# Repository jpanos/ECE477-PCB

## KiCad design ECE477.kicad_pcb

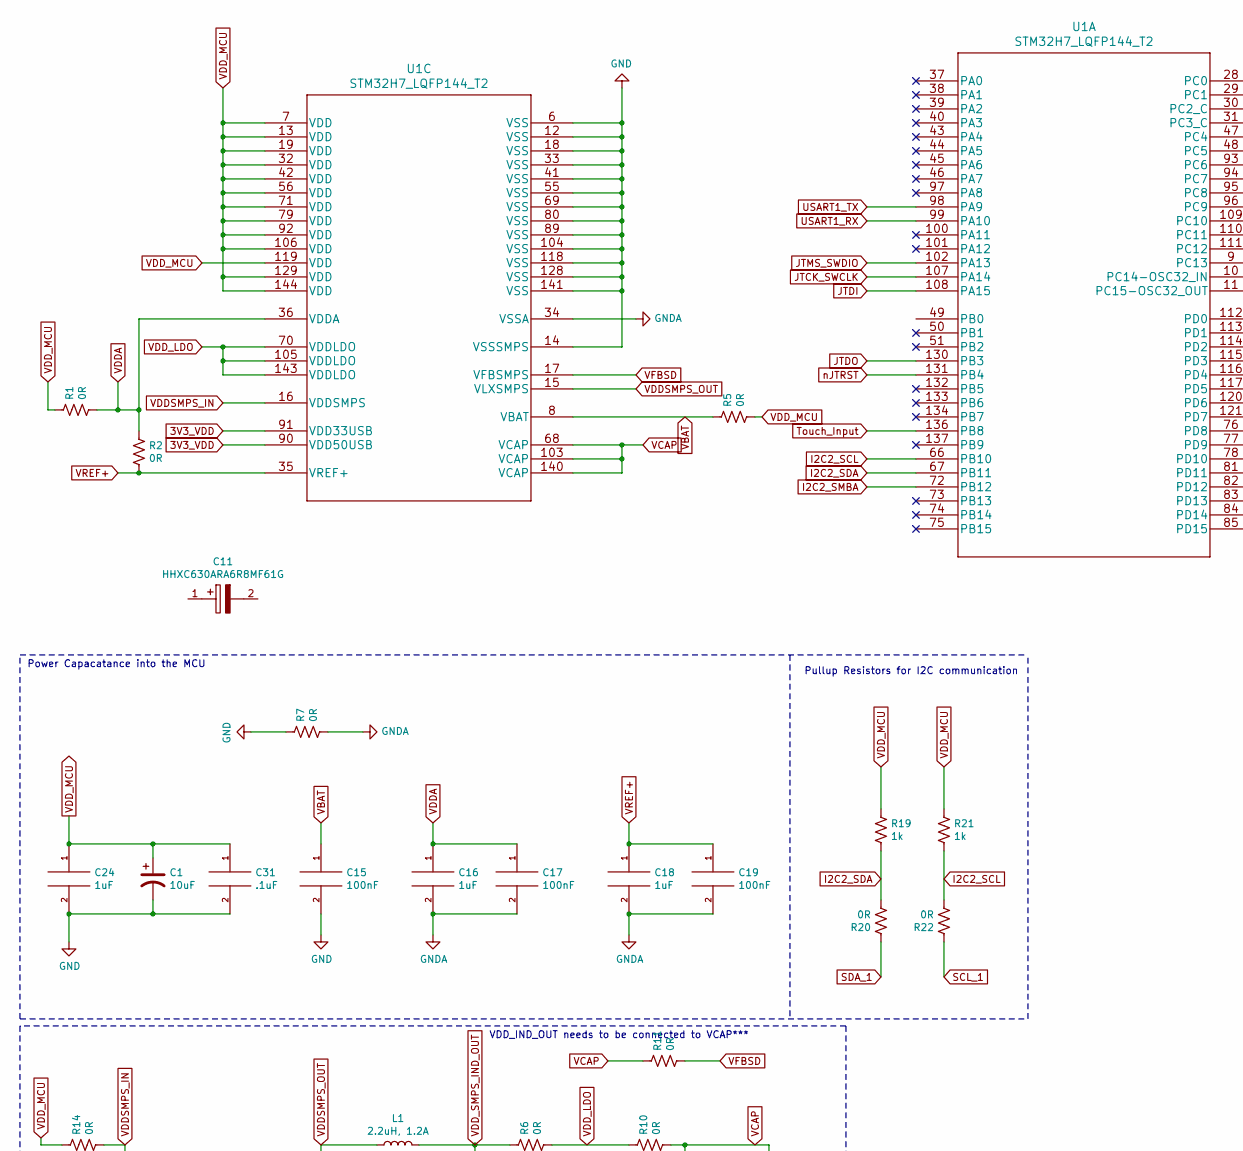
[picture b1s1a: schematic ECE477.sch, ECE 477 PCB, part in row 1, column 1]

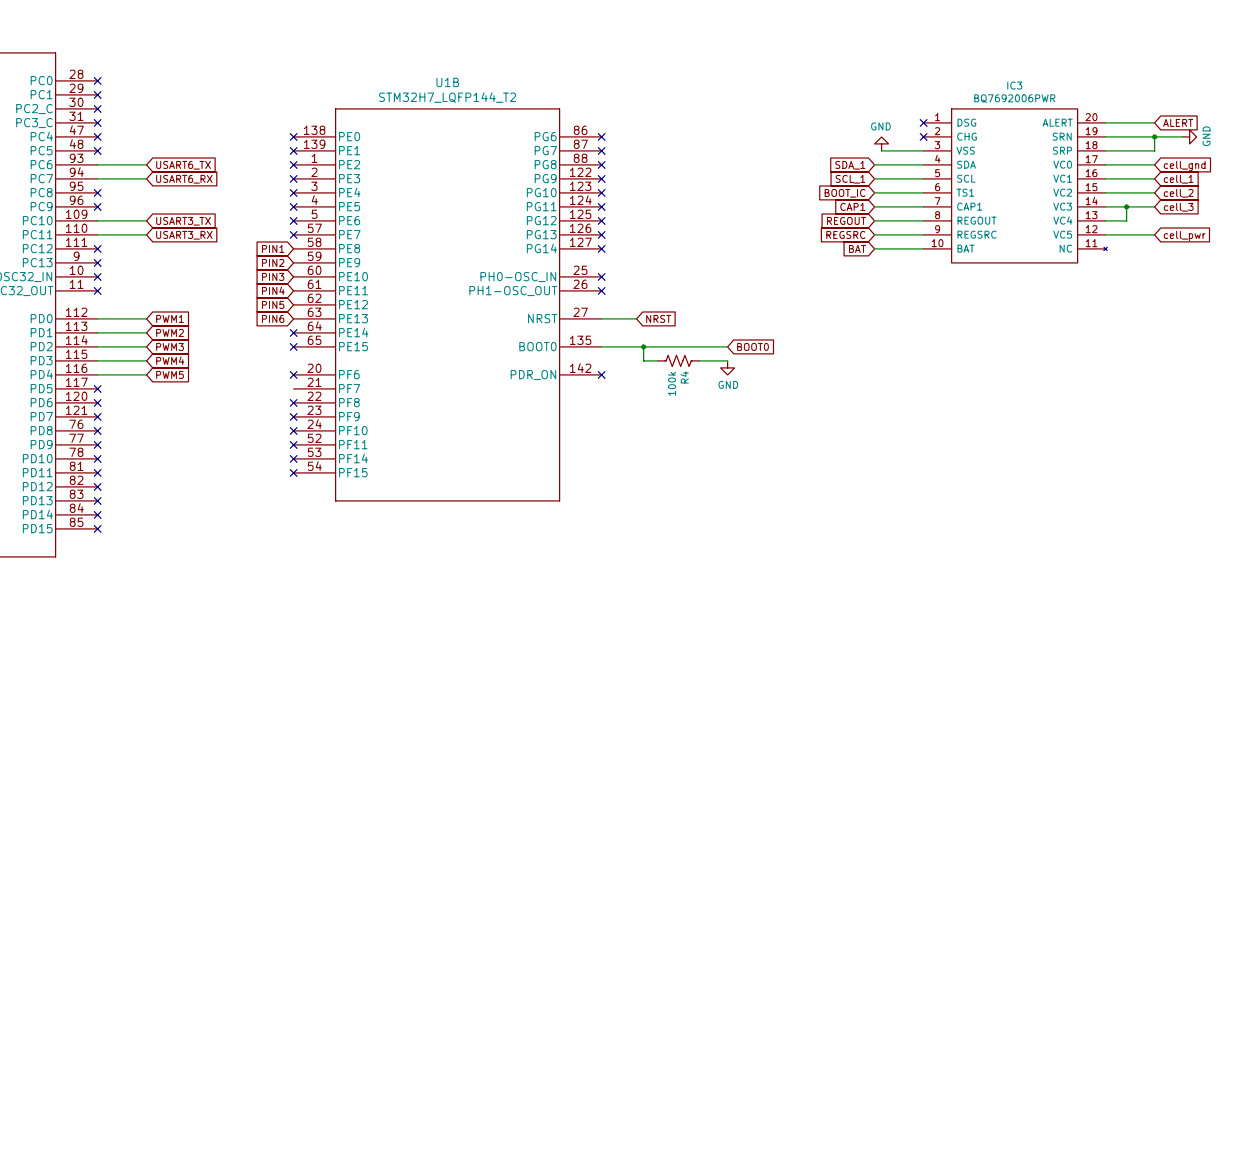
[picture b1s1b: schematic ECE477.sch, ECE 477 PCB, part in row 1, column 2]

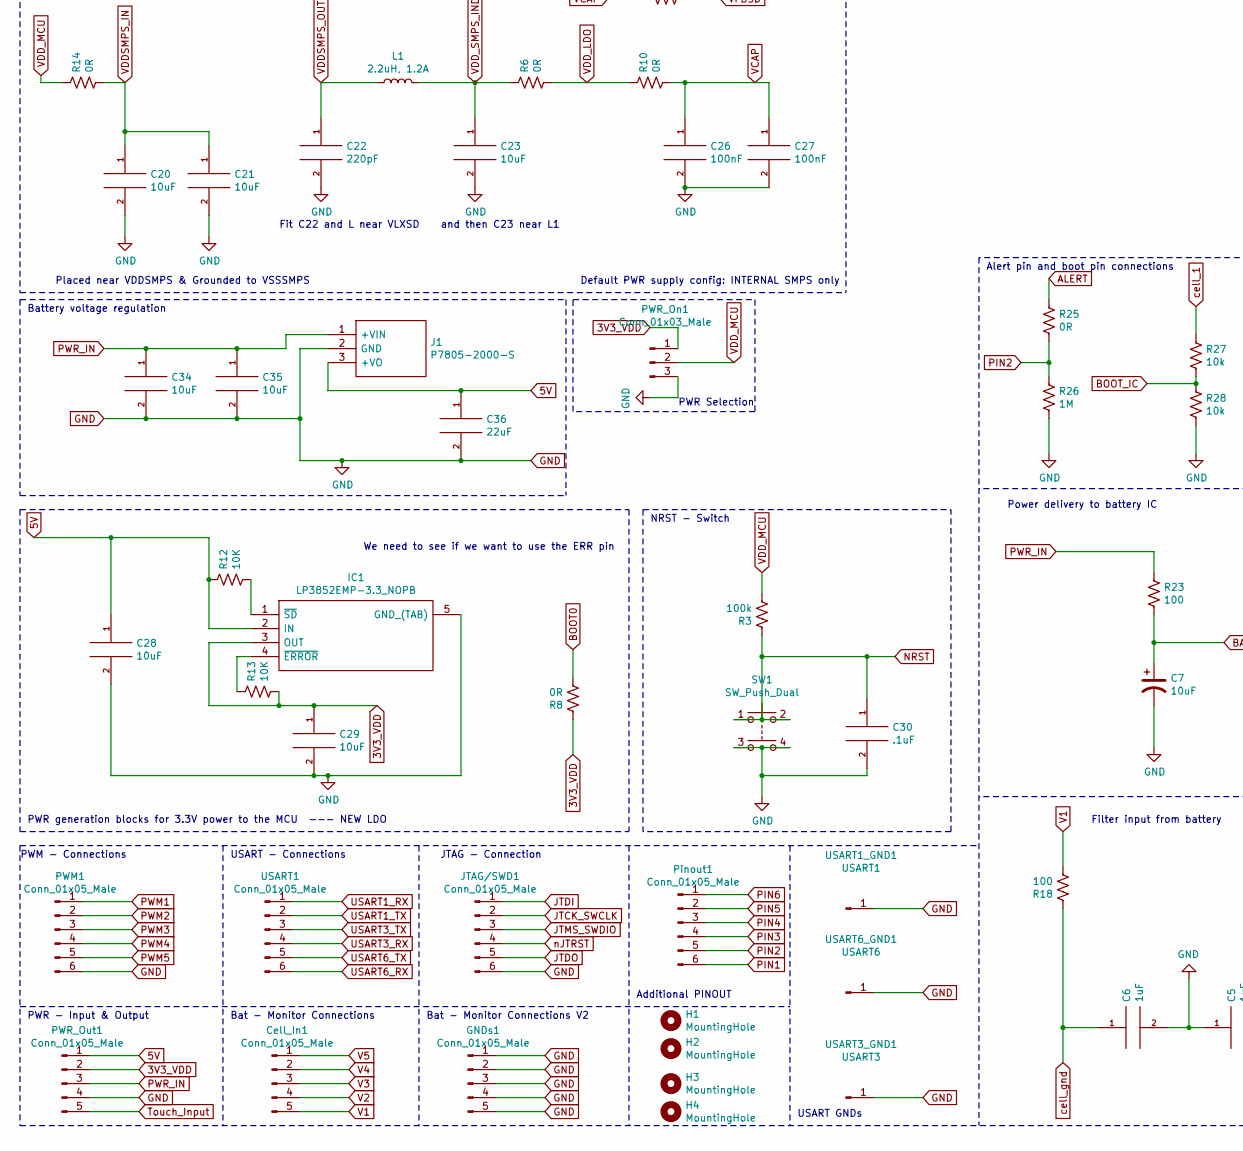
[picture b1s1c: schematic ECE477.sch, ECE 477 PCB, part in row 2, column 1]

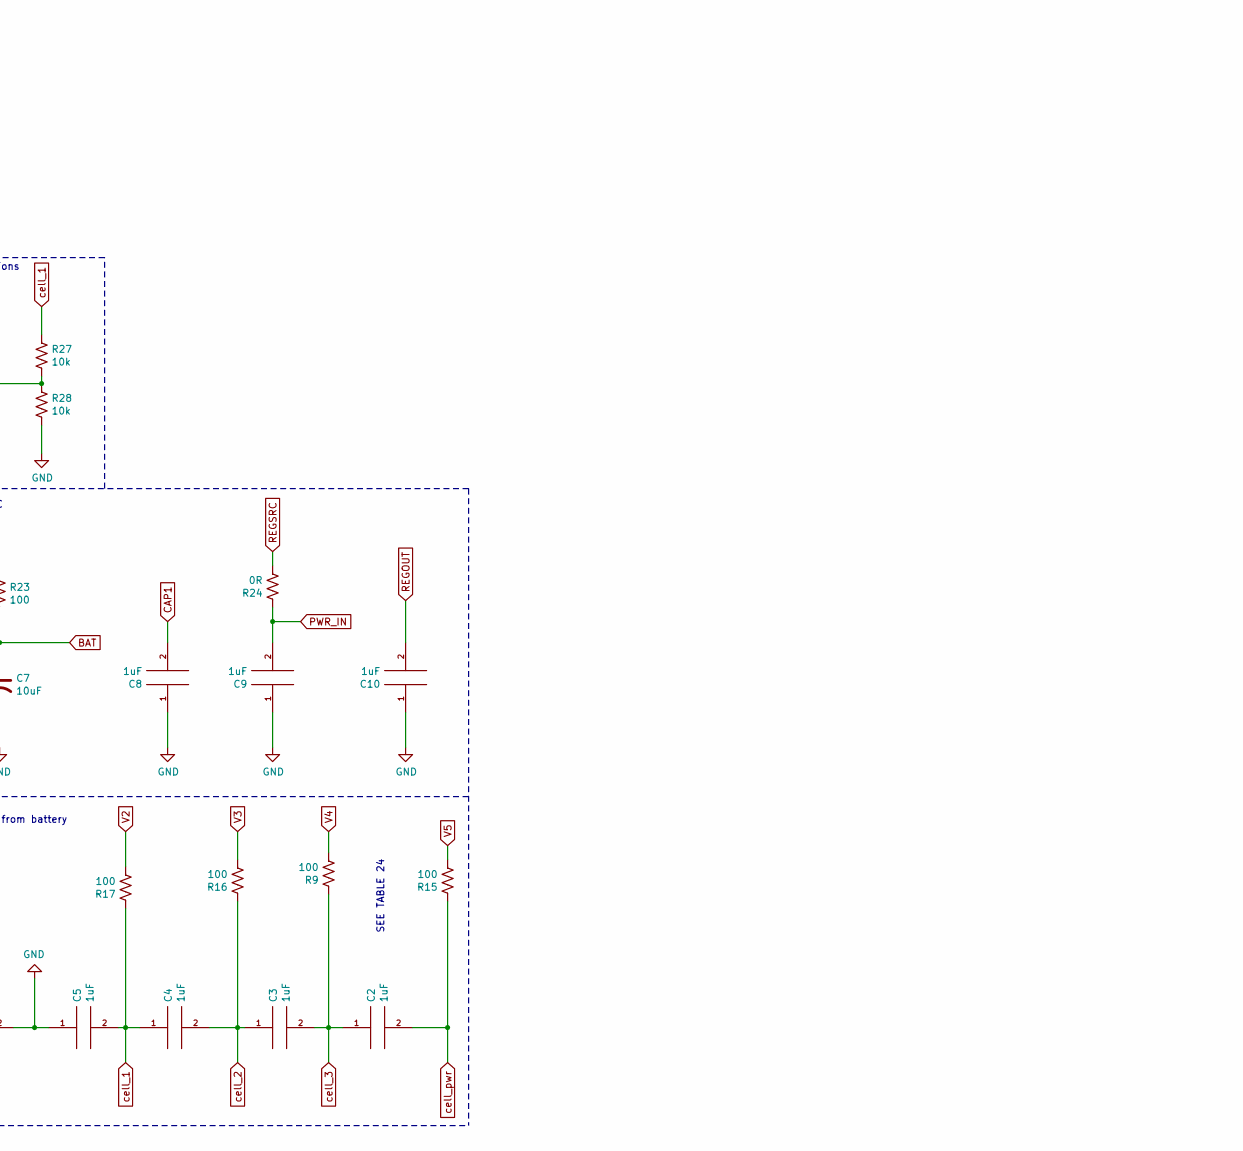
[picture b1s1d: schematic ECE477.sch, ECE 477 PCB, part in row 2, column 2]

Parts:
C1, C7: 10uF; CP_Radial_D5.0mm_P2.50mm
C2, C3, C4, C5, C6, C8, C9, C10, C16, C18, C24: 1uF; C_0805_2012Metric_Pad1.15x1.40mm_HandSolder
C11: HHXC630ARA6R8MF61G; CAPAE660X610N; Mouser Part Number 661-HHXC630A6R8MF61G
C15, C17, C19, C26, C27: 100nF; C_0805_2012Metric_Pad1.15x1.40mm_HandSolder
C20, C21, C23, C28, C29, C34, C35: 10uF; C_0805_2012Metric_Pad1.15x1.40mm_HandSolder
C22: 220pF; C_0805_2012Metric_Pad1.15x1.40mm_HandSolder
C30, C31: .1uF; C_0805_2012Metric_Pad1.15x1.40mm_HandSolder
C36: 22uF; C_0805_2012Metric_Pad1.15x1.40mm_HandSolder
Cell_In1: Conn_01x05_Male; PinHeader_1x05_P2.54mm_Vertical
GNDs1: Conn_01x05_Male; PinHeader_1x05_P2.54mm_Vertical
H1, H2, H3, H4: MountingHole; MountingHole_3.2mm_M3_ISO14580
IC1: LP3852EMP-3.3_NOPB; SOT150P700X180-5N; Mouser Part Number 926-LP3852EMP33NOPB
IC3: BQ7692006PWR; SOP65P640X120-20N; Mouser Part Number 595-BQ7692006PWR
J1: P7805-2000-S; P78052000S; Mouser Part Number 490-P7805-2000-S
JTAG/SWD1: Conn_01x05_Male; PinHeader_1x06_P2.54mm_Vertical
L1: 2.2uH, 1.2A; L_0805_2012Metric_Pad1.15x1.40mm_HandSolder
PWM1: Conn_01x05_Male; PinHeader_1x06_P2.54mm_Vertical
PWR_On1: Conn_01x03_Male; PinHeader_1x03_P2.54mm_Vertical
PWR_Out1: Conn_01x05_Male; PinHeader_1x05_P2.54mm_Vertical
Pinout1: Conn_01x05_Male; PinHeader_1x06_P2.54mm_Vertical
R1, R2, R5, R6, R7, R8, R10, R11, R14, R20, R22, R24, R25: 0R; R_0805_2012Metric_Pad1.15x1.40mm_HandSolder
R3, R4: 100k; R_0805_2012Metric_Pad1.15x1.40mm_HandSolder
R9, R15, R16, R17, R18, R23: 100; R_0805_2012Metric_Pad1.15x1.40mm_HandSolder
R12, R13: 10K; R_0805_2012Metric_Pad1.15x1.40mm_HandSolder
R19, R21: 1k; R_0805_2012Metric_Pad1.15x1.40mm_HandSolder
R26: 1M; R_0805_2012Metric_Pad1.15x1.40mm_HandSolder
R27, R28: 10k; R_0805_2012Metric_Pad1.15x1.40mm_HandSolder
SW1: SW_Push_Dual; SW_TH_Tactile_Omron_B3F-10xx
U1: STM32H7_LQFP144_T2
USART1: Conn_01x05_Male; PinHeader_1x06_P2.54mm_Vertical
USART1_GND1: USART1; PinHeader_1x01_P2.54mm_Vertical
USART3_GND1: USART3; PinHeader_1x01_P2.54mm_Vertical
USART6_GND1: USART6; PinHeader_1x01_P2.54mm_Vertical

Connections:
3V3_VDD: C29.1, IC1.3 (OUT), PWR_On1.1, PWR_Out1.2, R8.1, R13.2, U1.90 (VDD50USB), U1.91 (VDD33USB)
5V: C28.1, C36.1, IC1.2 (IN), J1.3 (+VO), PWR_Out1.1, R12.1
ALERT: IC3.20 (ALERT), R25.1
BAT: C7.1, IC3.10 (BAT), R23.2
BOOT0: R4.2, R8.2, U1.135 (BOOT0)
BOOT_IC: IC3.6 (TS1), R27.2, R28.1
CAP1: C8.2, IC3.7 (CAP1)
GND: C1.2, C5.1, C6.2, C7.2, C8.1, C9.1, C10.1, C15.2, C20.2, C21.2, C22.2, C23.2, C24.2, C26.2, C27.2, C28.2, C29.2, C30.2, C31.2, C34.2, C35.2, C36.2, GNDs1.1, GNDs1.2, GNDs1.3, GNDs1.4, GNDs1.5, IC1.5 (GND_(TAB)), IC3.3 (VSS), IC3.18 (SRP), IC3.19 (SRN), J1.2 (GND), JTAG/SWD1.6, PWM1.6, PWR_On1.3, PWR_Out1.4, R4.1, R7.1, R26.2, R28.2, SW1.3, SW1.4, U1.6 (VSS), U1.12 (VSS), U1.14 (VSSSMPS), U1.18 (VSS), U1.33 (VSS), U1.41 (VSS), U1.55 (VSS), U1.69 (VSS), U1.80 (VSS), U1.89 (VSS), U1.104 (VSS), U1.118 (VSS), U1.128 (VSS), U1.141 (VSS), USART1_GND1.1, USART3_GND1.1, USART6_GND1.1
GNDA: C16.2, C17.2, C18.2, C19.2, R7.2, U1.34 (VSSA)
I2C2_SCL: R21.2, R22.2, U1.66 (PB10)
I2C2_SDA: R19.2, R20.2, U1.67 (PB11)
I2C2_SMBA: U1.72 (PB12)
JTCK_SWCLK: JTAG/SWD1.2, U1.107 (PA14)
JTDI: JTAG/SWD1.1, U1.108 (PA15)
JTDO: JTAG/SWD1.5, U1.130 (PB3)
JTMS_SWDIO: JTAG/SWD1.3, U1.102 (PA13)
NRST: C30.1, R3.1, SW1.1, SW1.2, U1.27 (NRST)
unnamed: IC1.1 (~SD), R12.2
unnamed: IC1.4 (~ERROR), R13.1
PIN1: Pinout1.6, U1.58 (PE8)
PIN2: Pinout1.5, R25.2, R26.1, U1.59 (PE9)
PIN3: Pinout1.4, U1.60 (PE10)
PIN4: Pinout1.3, U1.61 (PE11)
PIN5: Pinout1.2, U1.62 (PE12)
PIN6: Pinout1.1, U1.63 (PE13)
PWM1: PWM1.1, U1.112 (PD0)
PWM2: PWM1.2, U1.113 (PD1)
PWM3: PWM1.3, U1.114 (PD2)
PWM4: PWM1.4, U1.115 (PD3)
PWM5: PWM1.5, U1.116 (PD4)
PWR_IN: C9.2, C34.1, C35.1, J1.1 (+VIN), PWR_Out1.3, R23.1, R24.1
REGOUT: C10.2, IC3.8 (REGOUT)
REGSRC: IC3.9 (REGSRC), R24.2
SCL_1: IC3.5 (SCL), R22.1
SDA_1: IC3.4 (SDA), R20.1
Touch_Input: PWR_Out1.5, U1.136 (PB8)
USART1_RX: U1.99 (PA10), USART1.1
USART1_TX: U1.98 (PA9), USART1.2
USART3_RX: U1.110 (PC11), USART1.4
USART3_TX: U1.109 (PC10), USART1.3
USART6_RX: U1.94 (PC7), USART1.6
USART6_TX: U1.93 (PC6), USART1.5
V1: Cell_In1.5, R18.2
V2: Cell_In1.4, R17.2
V3: Cell_In1.3, R16.2
V4: Cell_In1.2, R9.2
V5: Cell_In1.1, R15.2
VBAT: C15.1, R5.1, U1.8 (VBAT)
VCAP: C26.1, C27.1, R10.2, R11.1, U1.68 (VCAP), U1.103 (VCAP), U1.140 (VCAP)
VDDA: C16.1, C17.1, R1.2, R2.1, U1.36 (VDDA)
VDDSMPS_IN: C20.1, C21.1, R14.2, U1.16 (VDDSMPS)
VDDSMPS_OUT: C22.1, L1.1, U1.15 (VLXSMPS)
VDD_LDO: R6.2, R10.1, U1.70 (VDDLDO), U1.105 (VDDLDO), U1.143 (VDDLDO)
VDD_MCU: C1.1, C24.1, C31.1, PWR_On1.2, R1.1, R3.2, R5.2, R14.1, R19.1, R21.1, U1.7 (VDD), U1.13 (VDD), U1.19 (VDD), U1.32 (VDD), U1.42 (VDD), U1.56 (VDD), U1.71 (VDD), U1.79 (VDD), U1.92 (VDD), U1.106 (VDD), U1.119 (VDD), U1.129 (VDD), U1.144 (VDD)
VDD_SMPS_IND_OUT: C23.1, L1.2, R6.1
VFBSD: R11.2, U1.17 (VFBSMPS)
VREF+: C18.1, C19.1, R2.2, U1.35 (VREF+)
cell_1: C4.1, C5.2, IC3.16 (VC1), R17.1, R27.1
cell_2: C3.1, C4.2, IC3.15 (VC2), R16.1
cell_3: C2.1, C3.2, IC3.13 (VC4), IC3.14 (VC3), R9.1
cell_gnd: C6.1, IC3.17 (VC0), R18.1
cell_pwr: C2.2, IC3.12 (VC5), R15.1
nJTRST: JTAG/SWD1.4, U1.131 (PB4)

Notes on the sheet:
Placed near VDDSMPS & Grounded to VSSSMPS
Fit C22 and L near VLXSD and then C23 near L1
Default PWR supply config: INTERNAL SMPS only
VDD_IND_OUT needs to be connected to VCAP***
Battery voltage regulation
PWR Selection
Power Capacatance into the MCU
Bat - Monitor Connections
PWR - Input & Output
NRST - Switch
PWM - Connections
USART - Connections
JTAG - Connection
PWR generation blocks for 3.3V power to the MCU --- NEW LDO
We need to see if we want to use the ERR pin
Bat - Monitor Connections V2
USART GNDs
Additional PINOUT
SEE TABLE 24
Filter input from battery
Power delivery to battery IC
Pullup Resistors for I2C communication
Alert pin and boot pin connections

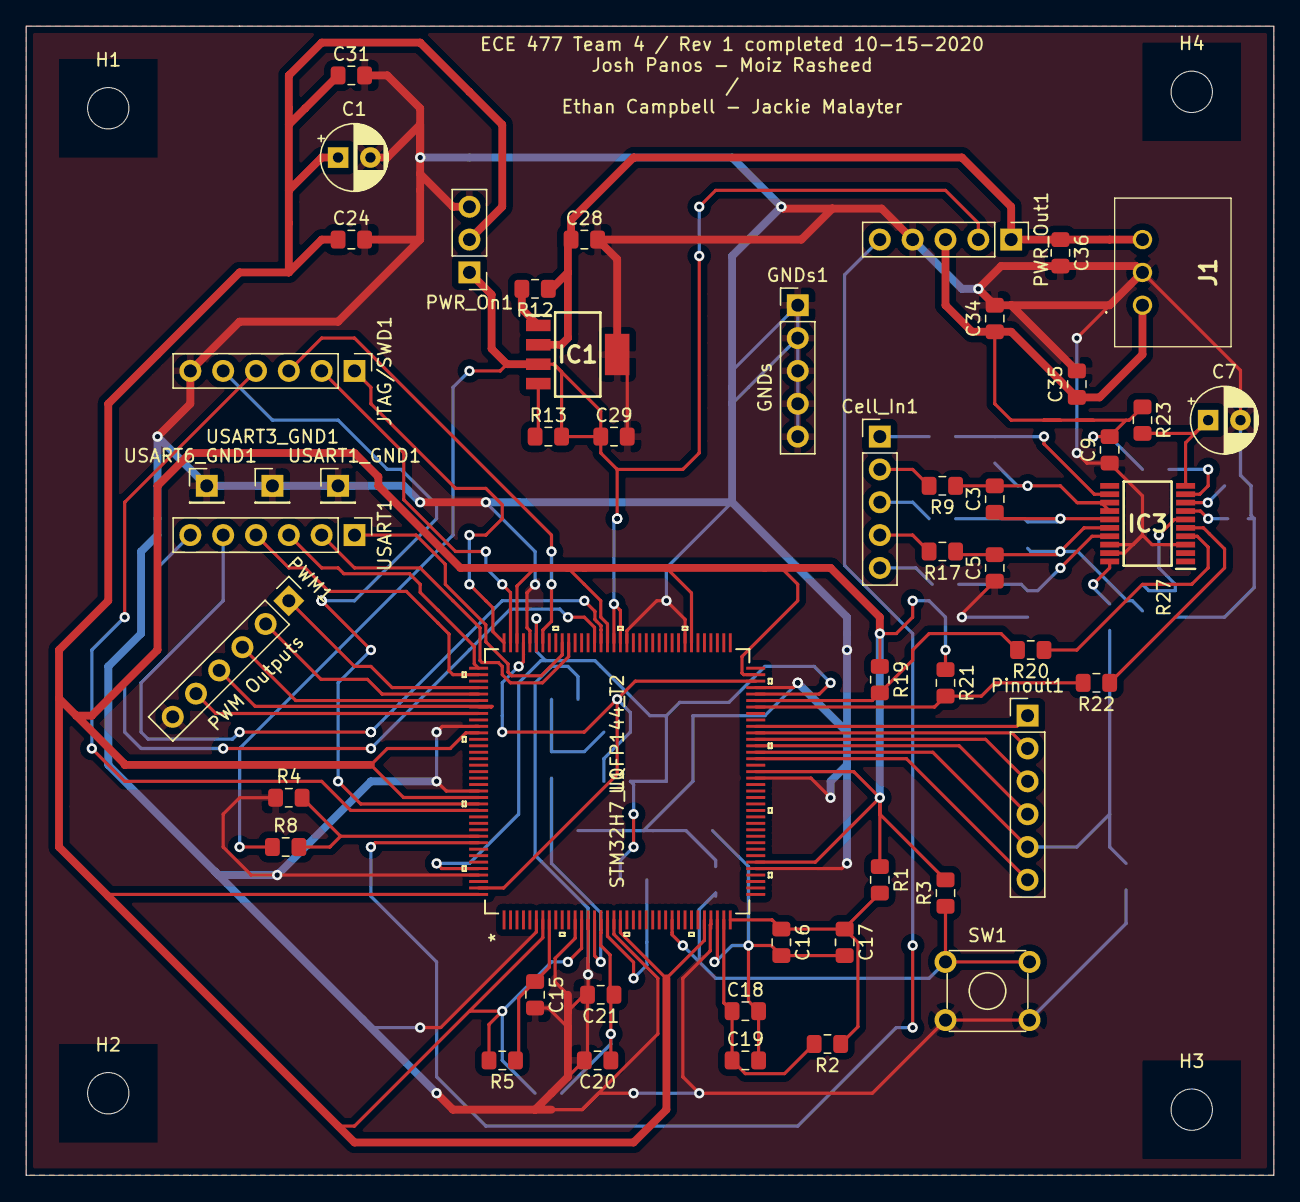
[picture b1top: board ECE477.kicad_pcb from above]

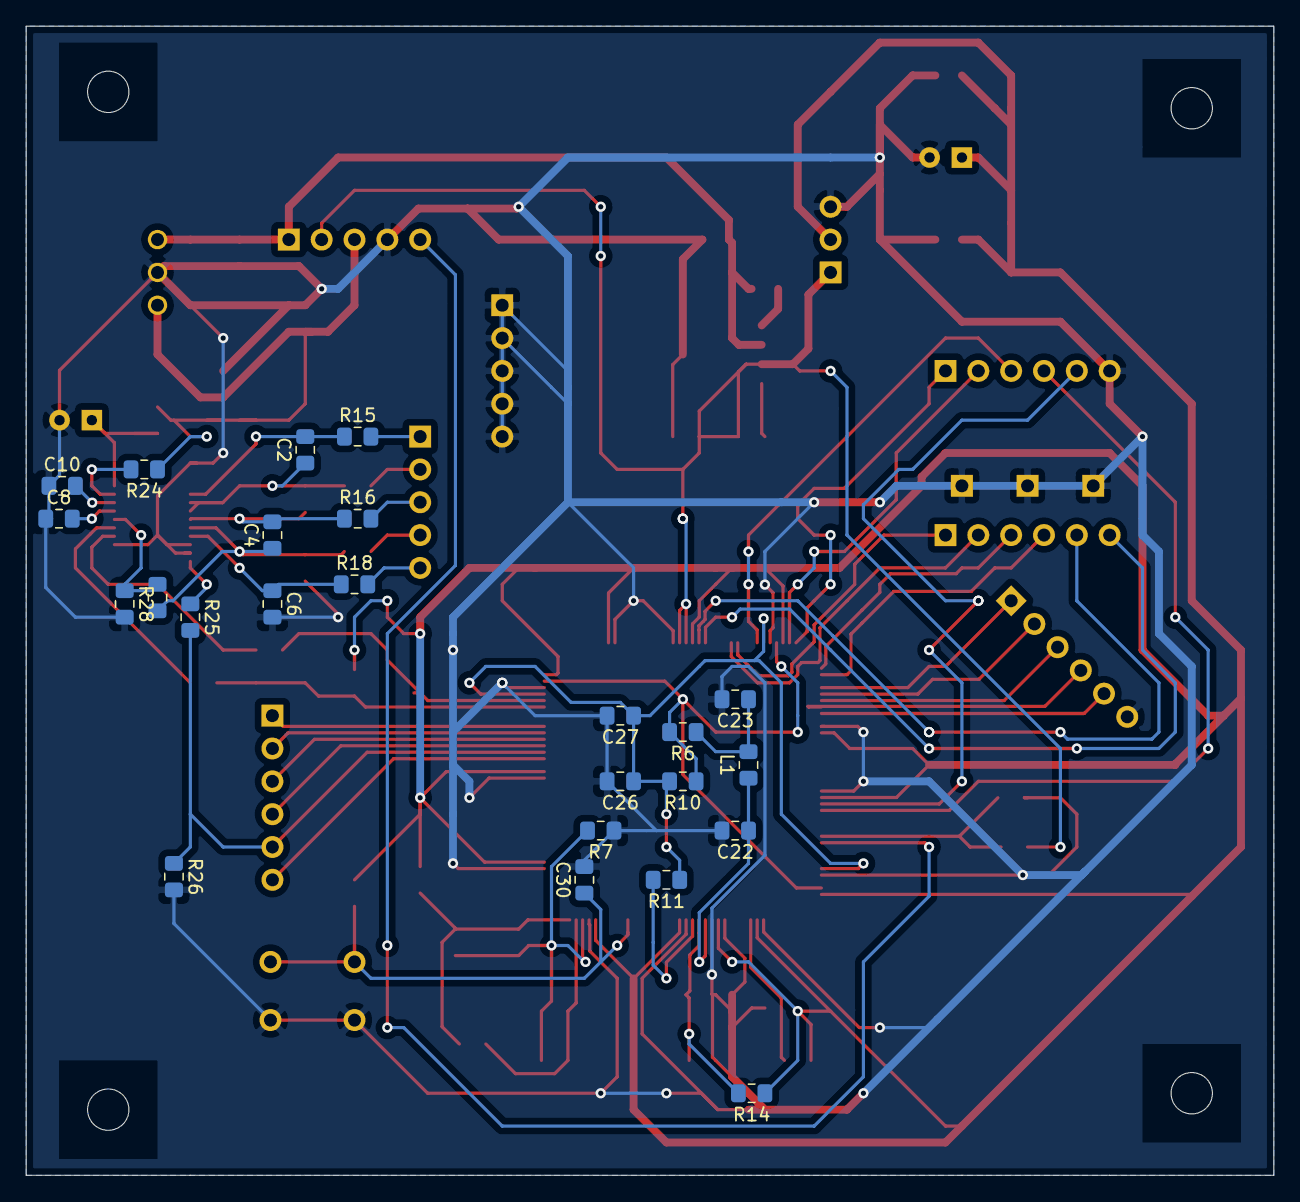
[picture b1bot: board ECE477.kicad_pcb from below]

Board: 2 copper layers, 96.5 x 88.9 mm, 78 parts (24 on the bottom side), 62 nets.

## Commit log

2020-09-20 Working PCB code
2020-09-21 Adding in libraies
2020-09-21 ALl libaries
    Added all libaries used for the current KiCAD
2020-09-21 Added Power Scheme 2
    Default power scheme added with SMPS on and LDO off.
2020-09-21 Updated
    Annotated Schematic
2020-09-21 Adding new librarys
    Added new libraries for more PCB power delivery. Also continuing to update PCB PWR wiring with 3.3 and 1.8V generation
2020-09-21 Rapair
    Repaired Libary miss configuration Should no longer be issues with loading the STM32
2020-09-21 Added 3.3V and 1.8V power generation
2020-09-21 Added pins for JTAG & USART1
2020-09-22 Added in Battery Regulator
2020-09-22 New battery monitor
    Changed thebattery monitor IC to a similar one due to first chip not beign avaliable
2020-09-24 Footprints
    Added footprints to all componets and changed some library associations around.
2020-09-24 Removing the 1V8 pwr supply
2020-09-24 Adding info to battery monitor
2020-09-28 Working on PCB
    Working on layout
2020-09-28 Wiring for the NEW LDO
2020-09-28 FIxing issues with the schematic import that I did not notice
2020-09-28 Added what needs to be done on schematic
2020-09-30 Adding NRST + Boot
    Added NRST + Boot
2020-09-30 Pinouts
    Pin outs for USART GPIO and JTAG
2020-09-30 Added Pinout
    Added footprints and pinout connections
2020-10-01 Updated post review with team members
2020-10-01 Finalized Pinout
2020-10-01 Label and layout updates
    Updated Labesl for simplicity along with a starting footprint layout for our PCB.
2020-10-01 Post meeting with TODD
2020-10-02 Updated PACK and BAT
2020-10-05 Updated Bat monitor
2020-10-05 Working with Routing
2020-10-07 Finshed Routing One
2020-10-07 updated NRST capacitor location closer to MCU
2020-10-08 review with team
2020-10-08 Added ground planes
2020-10-08 filled zones
2020-10-08 Updated CLK for Bq29330DBT
2020-10-08 Added mounting Holes
2020-10-08 Updates #1 post meeting with TODD
    Updated pins and added GNDs for serial communication refreces.
2020-10-10 Updated with single cap
2020-10-13 Shrunk PCB size
2020-10-14 Added additional outputs on GPIOE
2020-10-15 Updated USART GND
2020-10-15 Update with pins
2020-10-15 DRC corrections
2020-10-15 Board label
2020-10-18 naming
2020-10-23 Major change
2020-10-23 Updated layout
2020-10-23 Fixed DRC issue
2020-10-23 Changed mounting holes
2020-10-23 Updates post meeting with Todd
2020-10-26 Generated Gerbers
2020-12-28 Set theme jekyll-theme-cayman

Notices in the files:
parts and their libraries:
Copyright 2016 Accelerated Designs. All rights reserved.
